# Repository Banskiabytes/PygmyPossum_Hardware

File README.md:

[![Contributors][contributors-shield]][contributors-url]
[![Forks][forks-shield]][forks-url]
[![Stargazers][stars-shield]][stars-url]
[![Issues][issues-shield]][issues-url]
[![MIT License][license-shield]][license-url]
[![LinkedIn][linkedin-shield]][linkedin-url]

<!-- PROJECT LOGO -->
<br />
<p align="center">

  <h3 align="center">The Pygmy Possum</h3>
  <p align="center">PIR sensor for camera traps</p>
</p>

<!-- TABLE OF CONTENTS -->
## Table of Contents

* [About the Project](#about-the-project)
* [Built With](#built-with)
* [Usage](#usage)
* [License](#license)
* [Contact](#contact)

<!-- ABOUT THE PROJECT -->
## About The Project

## Built With
#### Software:
* [KiCAD]

<!-- USAGE EXAMPLES -->
## Usage

Set the DIP switches on the front of the board to select your pre-programmed package. There are 8 pre-progammed packages in total. Each package contains a value for:
* Number of Shots to take after a Event
* Time Between Shots
* Minimum time between Events

<!-- LICENSE -->
## License

Distributed under the MIT License. See `LICENSE` for more information.

<!-- CONTACT -->
## Contact

* Tom Evison - tom@evisonengineering.com.au
* James Lidsey - james.lidsey93@gmail.com

<!-- MARKDOWN LINKS & IMAGES -->
<!-- https://www.markdownguide.org/basic-syntax/#reference-style-links -->
[contributors-shield]: https://img.shields.io/github/contributors/tomevison/repo.svg?style=flat-square
[contributors-url]: https://github.com/tomevison/PYGMY/graphs/contributors
[forks-shield]: https://img.shields.io/github/forks/tomevison/repo.svg?style=flat-square
[forks-url]: https://github.com/tomevison/repo/network/members
[stars-shield]: https://img.shields.io/github/stars/tomevison/repo.svg?style=flat-square
[stars-url]: https://github.com/tomevison/repo/stargazers
[issues-shield]: https://img.shields.io/github/issues/tomevison/repo.svg?style=flat-square
[issues-url]: https://github.com/EmbeddedEnvironmental/PygmyPossum_Firmware/issues
[license-shield]: https://img.shields.io/github/license/tomevison/repo.svg?style=flat-square
[license-url]: https://github.com/EmbeddedEnvironmental/PygmyPossum_Firmware/blob/master/LICENSE
[linkedin-shield]: https://img.shields.io/badge/-LinkedIn-black.svg?style=flat-square&logo=linkedin&colorB=555
[linkedin-url]: https://www.linkedin.com/in/thomas-evison-87b27073/# Hardware

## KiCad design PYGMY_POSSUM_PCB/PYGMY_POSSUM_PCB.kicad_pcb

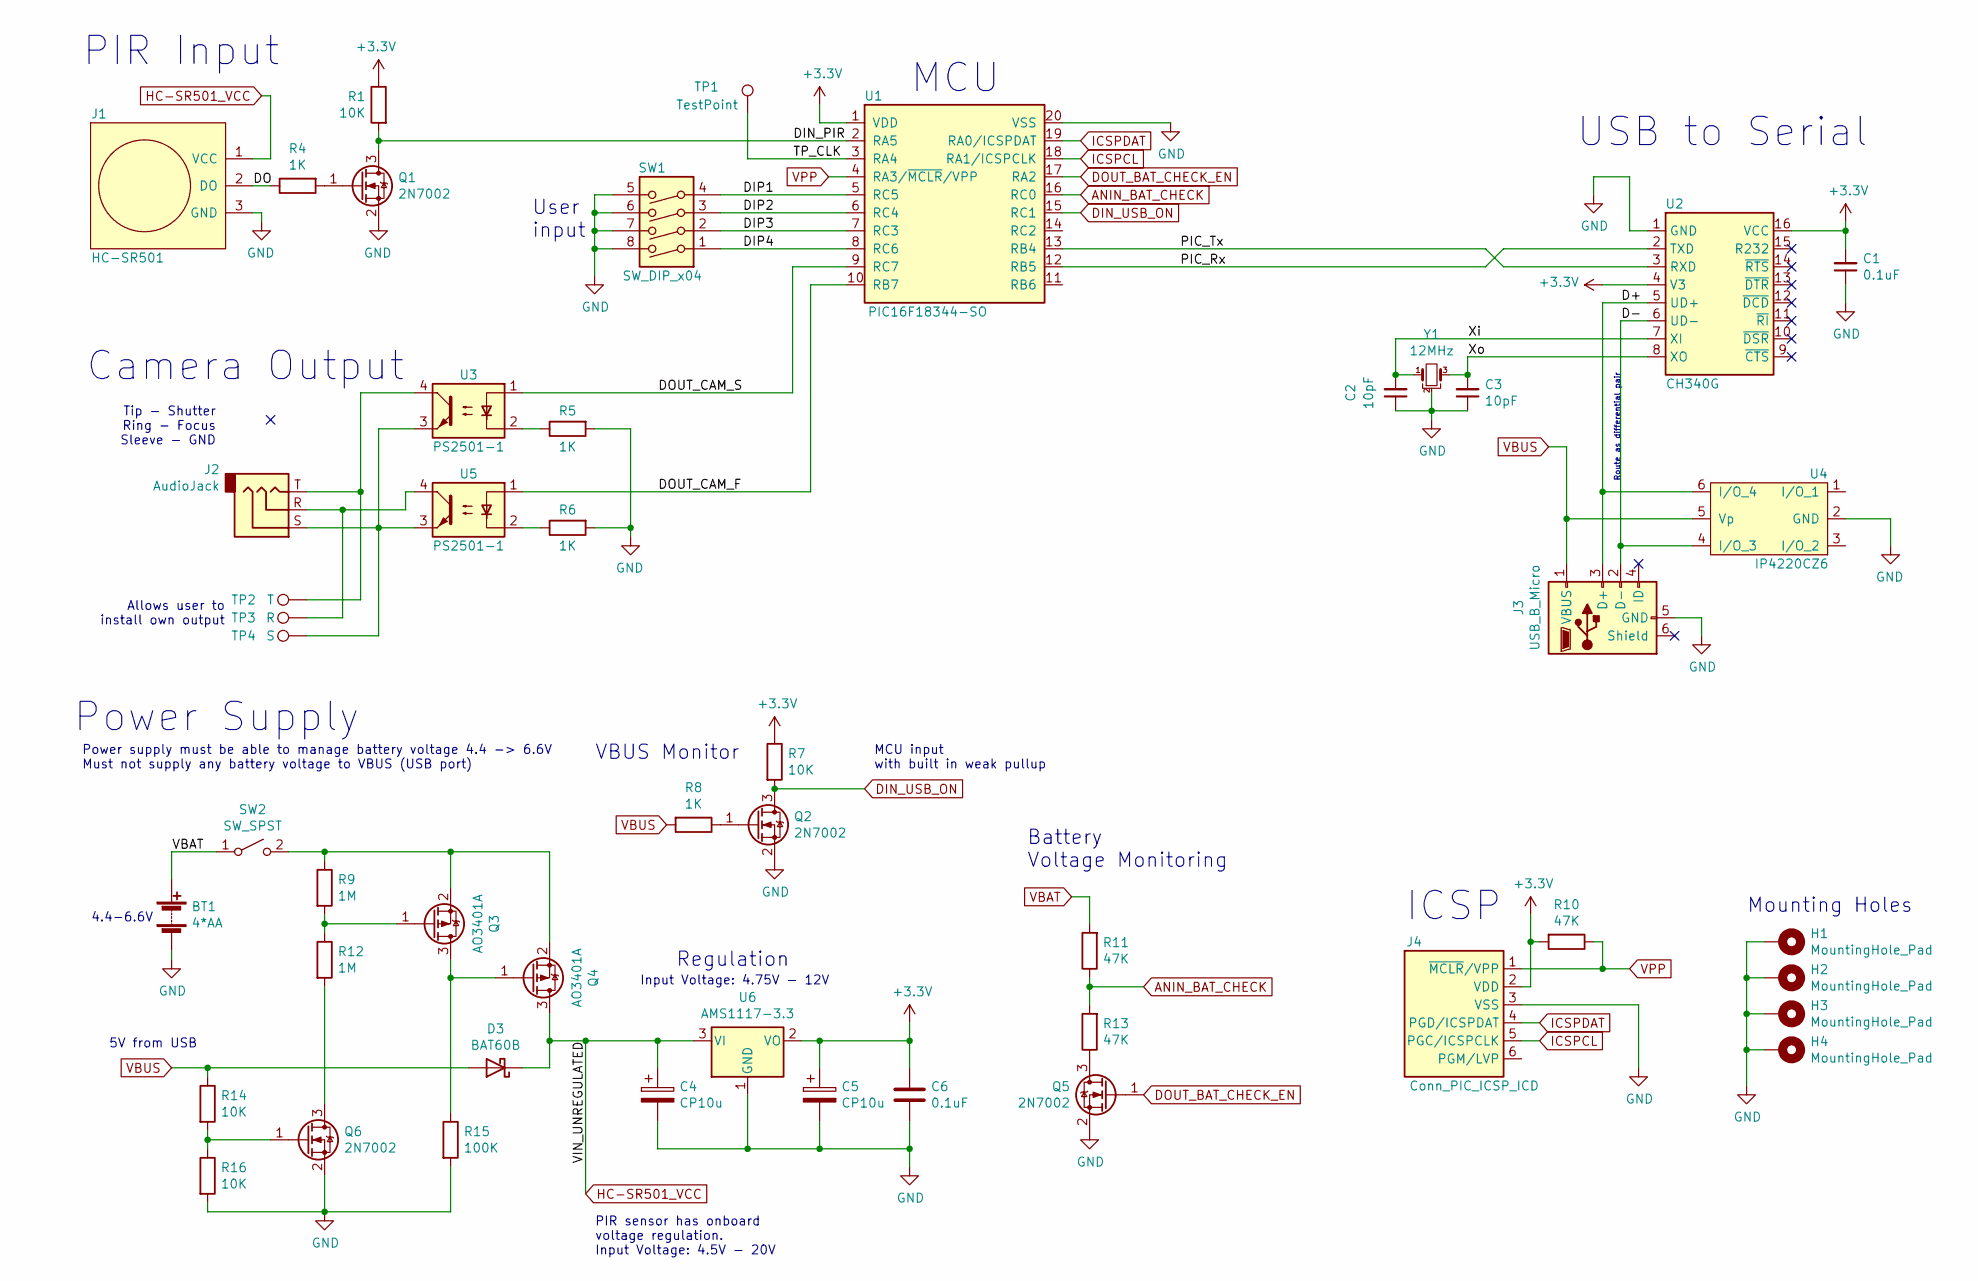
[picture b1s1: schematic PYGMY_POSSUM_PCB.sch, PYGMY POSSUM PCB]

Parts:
BT1: 4*AA; BatteryHolder_Keystone_2462_2xAA; MPN 2477
C1, C6: 0.1uF; C_0603_1608Metric; LCSC C14663
C2, C3: 10pF; C_0603_1608Metric; LCSC C1634
C4, C5: CP10u; CP_Elec_4x3.9; LCSC C134721
D3: BAT60B; D_SOD-323; LCSC C514095
H1, H2, H3, H4: MountingHole_Pad; MountingHole_3mm_Pad_Via
J1: HC-SR501
J2: AudioJack; Jack_3.5mm_CUI_SJ-3523-SMT_Horizontal; MPN SJ-3523-SMT-TR
J3: USB_B_Micro; USB_Micro-B_Molex-105017-0001; MPN 105017-0001
J4: Conn_PIC_ICSP_ICD; PinHeader_1x06_P2.54mm_Vertical
Q1, Q2, Q5, Q6: 2N7002; SOT-23; MPN 2N7002; LCSC C8545
Q3, Q4: AO3401A; SOT-23; MPN AO3401A; LCSC C15127
R1, R7, R14, R16: 10K; R_0805_2012Metric; LCSC C17414
R4, R5, R6, R8: 1K; R_0805_2012Metric; LCSC C17513
R9, R12: 1M; R_0805_2012Metric; LCSC C17514
R10, R11, R13: 47K; R_0805_2012Metric; LCSC C17713
R15: 100K; R_0805_2012Metric; LCSC C17407
SW1: SW_DIP_x04; SW_DIP_SPSTx04_Slide_6.7x11.72mm_W8.61mm_P2.54mm_LowProfile; MPN MCDM(R)-04-T
SW2: SW_SPST; SW_CuK_JS202011AQN_DPDT_Angled; MPN JS202011AQN
TP1: TestPoint; TestPoint_Pad_D1.0mm
TP2: T; TestPoint_Pad_2.5x2.5mm
TP3: R; TestPoint_Pad_2.5x2.5mm
TP4: S; TestPoint_Pad_2.5x2.5mm
U1: PIC16F18344-SO; SSOP-20_5.3x7.2mm_P0.65mm; MPN PIC16F18344-E/SS; LCSC C144347
U2: CH340G; SOIC-16_3.9x9.9mm_P1.27mm; MPN CH340G; LCSC C14267
U3, U5: PS2501-1; SOIC-4_4.55x2.6mm_P1.27mm; LCSC C51825
U4: IP4220CZ6; SOT457; MPN IP4220CZ6,125; LCSC C282546
U6: AMS1117-3.3; SOT-223-3_TabPin2; LCSC C6186
Y1: 12MHz; Crystal_SMD_3225-4Pin_3.2x2.5mm; LCSC C9002

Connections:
+3V3: C1.2, C5.1, C6.1, J4.2 (VDD), R1.1, R7.1, R10.2, U1.1 (VDD), U2.4 (V3), U2.16 (VCC), U6.2 (VO)
/D+: J3.3 (D+), U2.5 (UD+), U4.6 (I/O_4)
/D-: J3.2 (D-), U2.6 (UD-), U4.4 (I/O_3)
/DIN_PIR: Q1.3 (D), R1.2, U1.2 (RA5)
/DIP1: SW1.4, U1.5 (RC5)
/DIP2: SW1.3, U1.6 (RC4)
/DIP3: SW1.2, U1.7 (RC3)
/DIP4: SW1.1, U1.8 (RC6)
/DO: J1.2 (DO), R4.1
/DOUT_CAM_F: U1.10 (RB7), U5.1
/DOUT_CAM_S: U1.9 (RC7), U3.1
/PIC_Rx: U1.12 (RB5), U2.2 (TXD)
/PIC_Tx: U1.13 (RB4), U2.3 (RXD)
/TP_CLK: TP1.1, U1.3 (RA4)
/Xi: C2.2, U2.7 (XI), Y1.1
/Xo: C3.2, U2.8 (XO), Y1.3
ANIN_BAT_CHECK: R11.1, R13.2, U1.16 (RC0)
DIN_USB_ON: Q2.3 (D), R7.2, U1.15 (RC1)
DOUT_BAT_CHECK_EN: Q5.1 (G), U1.17 (RA2)
GND: BT1.2 (-), C1.1, C2.1, C3.1, C4.2, C5.2, C6.2, H1.1, H2.1, H3.1, H4.1, J1.3 (GND), J3.5 (GND), J4.3 (VSS), Q1.2 (S), Q2.2 (S), Q5.2 (S), Q6.2 (S), R5.2, R6.2, R15.2, R16.2, SW1.5, SW1.6, SW1.7, SW1.8, U1.20 (VSS), U2.1 (GND), U4.2 (GND), U6.1 (GND), Y1.2
HC-SR501_VCC: C4.1, D3.1 (K), J1.1 (VCC), Q4.3 (D), U6.3 (VI)
ICSPCL: J4.5 (PGC/ICSPCLK), U1.18 (RA1/ICSPCLK)
ICSPDAT: J4.4 (PGD/ICSPDAT), U1.19 (RA0/ICSPDAT)
unnamed: J2.R, TP3.1, U5.4
unnamed: J2.S, TP4.1, U3.3, U5.3
unnamed: J2.T, TP2.1, U3.4
unnamed: Q1.1 (G), R4.2
unnamed: Q2.1 (G), R8.1
unnamed: Q3.1 (G), R9.2, R12.1
unnamed: Q3.2 (S), Q4.2 (S), R9.1, SW2.2 (B)
unnamed: Q3.3 (D), Q4.1 (G), R15.1
unnamed: Q5.3 (D), R13.1
unnamed: Q6.1 (G), R14.2, R16.1
unnamed: Q6.3 (D), R12.2
unnamed: R5.1, U3.2
unnamed: R6.1, U5.2
VBAT: BT1.1 (+), R11.2, SW2.1 (A)
VBUS: D3.2 (A), J3.1 (VBUS), R8.2, R14.1, U4.5 (Vp)
VPP: J4.1 (~MCLR~/VPP), R10.1, U1.4 (RA3/~MCLR~/VPP)

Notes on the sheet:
ICSP
Tip - Shutter Ring - Focus Sleeve - GND
Camera Output
USB to Serial
Battery Voltage Monitoring
PIR Input
User input
Route as differential pair
MCU
Mounting Holes
Power supply must be able to manage battery voltage 4.4 -> 6.6V Must not supply any battery voltage to VBUS (USB port)
Power Supply
PIR sensor has onboard voltage regulation. Input Voltage: 4.5V - 20V
4.4-6.6V
Input Voltage: 4.75V - 12V
Regulation
5V from USB
MCU input with built in weak pullup
VBUS Monitor
Allows user to install own output

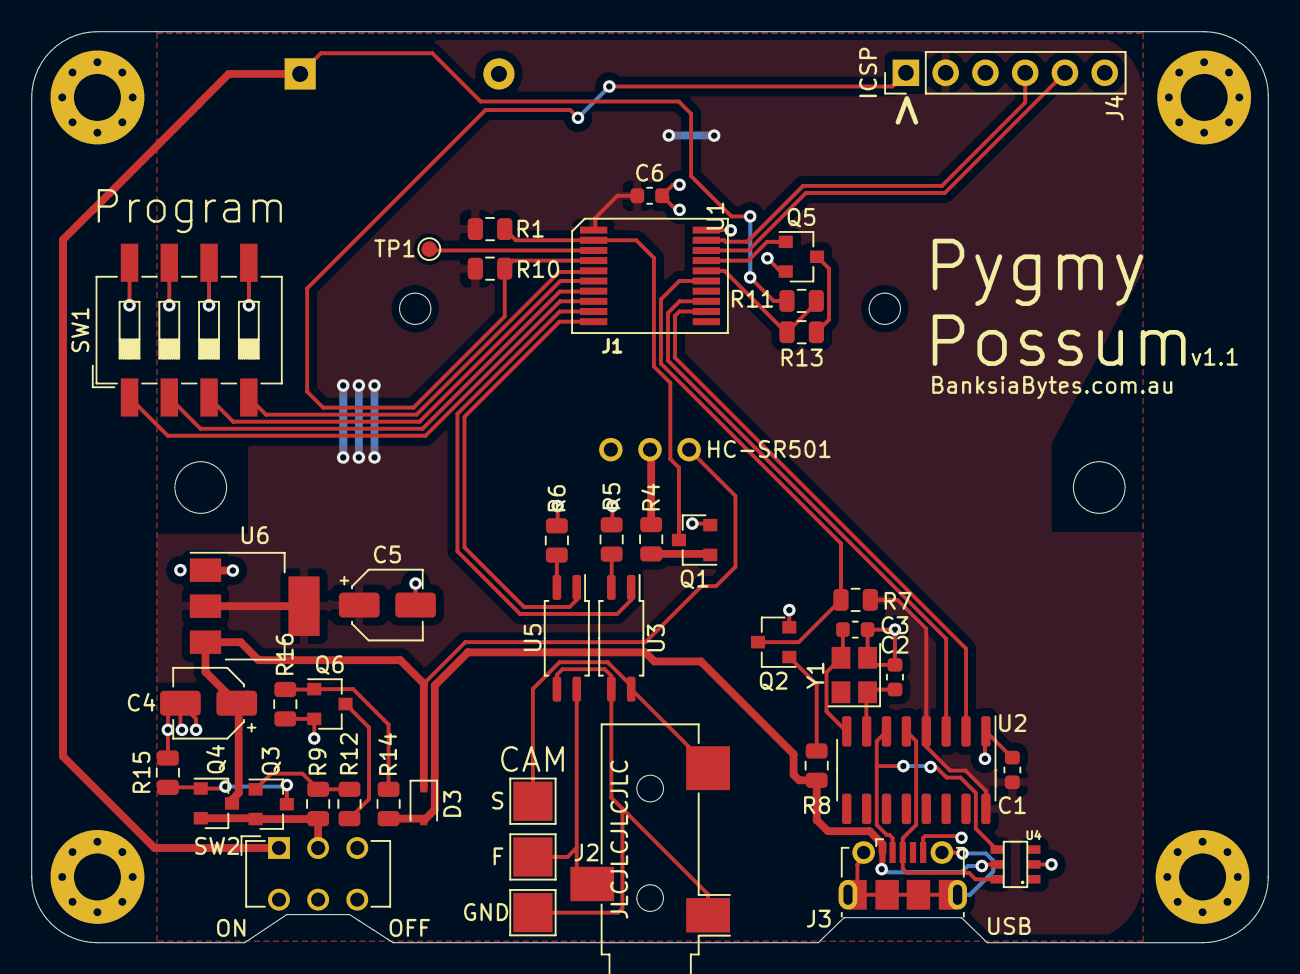
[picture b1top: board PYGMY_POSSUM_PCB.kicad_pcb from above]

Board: 2 copper layers, 79.0 x 58.2 mm, 49 parts (1 on the bottom side), 39 nets.

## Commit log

2020-10-19 added bulk of components
2020-10-20 Added OR logic to power supply. Added all external devices Upgraded MCU to PIC16F18344 to allow for aditional IO.
2020-10-20 added info to readme file
2021-03-25 updated PDF and added .stp file
2021-03-25 fixed upload location
